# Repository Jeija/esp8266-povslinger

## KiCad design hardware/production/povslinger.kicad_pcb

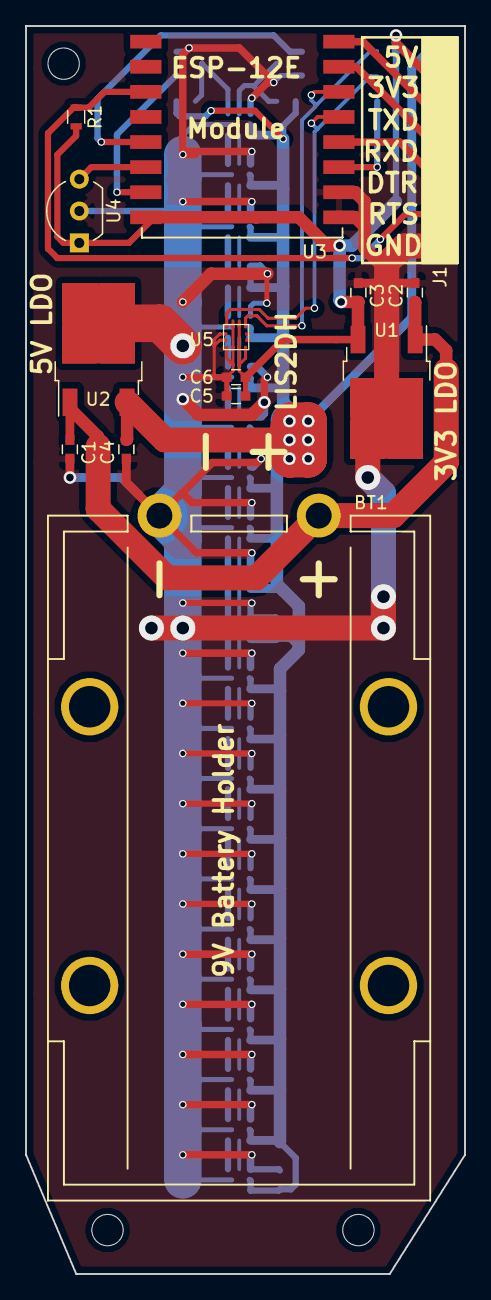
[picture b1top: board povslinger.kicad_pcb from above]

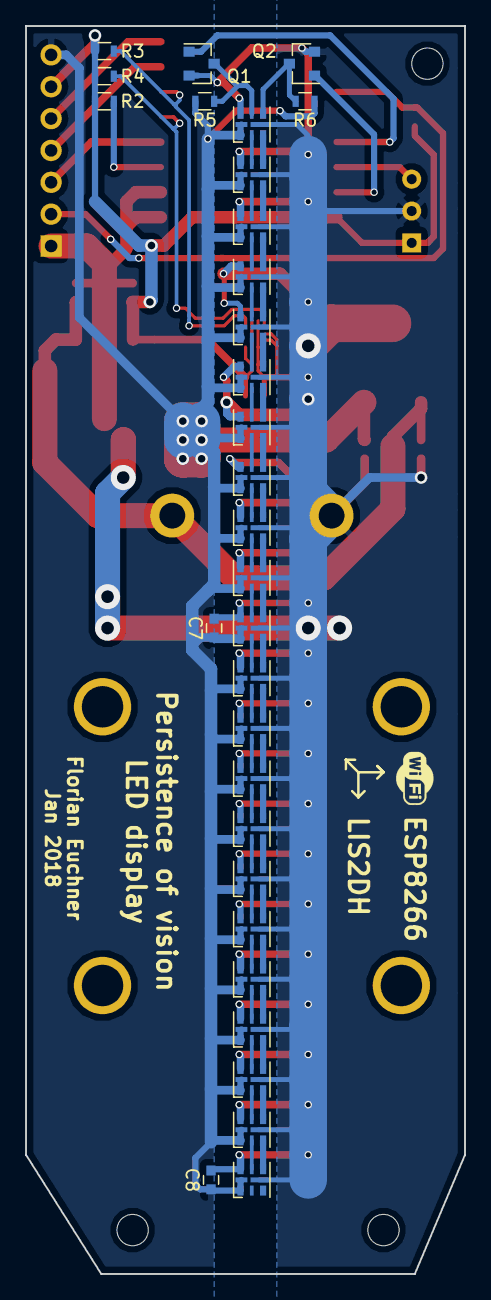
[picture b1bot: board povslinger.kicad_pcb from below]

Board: 2 copper layers, 35.0 x 99.5 mm, 45 parts (31 on the bottom side), 58 nets.

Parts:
BT1: 9V Battery; BatteryHolder_9Volt_Keystone_1294
C1, C2: 330n; C_0603
C3, C4: 4.7u; C_0603
C5: 10n; C_0603
C6, C7, C8: 100n; C_0603
D1, D2, D3, D4, D5, D6, D7, D8, D9, D10, D11, D12, D13, D14, D15, D16, D17, D18, D19, D20, D21, D22: APA102-2020
J1: DEBUG; Pin_Header_Straight_1x07_Pitch2.54mm
Q1, Q2: BSS138; SOT-23
R1, R2, R5, R6: 10K; R_0603
R3, R4: 4K7; R_0603
U1: LF33_TO252; TO-252-2
U2: L7805; TO-252-2
U3: ESP-12E; ESP-12E_SMD
U4: US5881 or similar; TO-92_Inline_Wide
U5: LIS2HH12; LIS2DH12

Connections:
+3V3: C3.1, C5.1, C6.1, J1.6, R1.1, R2.1, R3.1, R4.1, U1.3, U3.8, U4.1, U5.2, U5.9, U5.10
+5V: C4.1, C7.1, C8.1, D1.1, D2.1, D3.1, D4.1, D5.1, D6.1, D7.1, D8.1, D9.1, D10.1, D11.1, D12.1, D13.1, D14.1, D15.1, D16.1, D17.1, D18.1, D19.1, D20.1, D21.1, D22.1, J1.7, R5.1, R6.1, U2.3
+BATT: BT1.1, C1.1, C2.1, U1.1, U2.1
/DTR: J1.3, U3.12
/HALL: U3.6, U4.3
/LEDCLK: Q1.1, U3.5
/LEDCLK_5V: D1.5, Q1.3, R5.2
/LEDDAT: Q2.1, U3.7
/LEDDAT_5V: D1.4, Q2.3, R6.2
/RTS: J1.2, R1.2, U3.3
/RXD: J1.4, U3.15
/SCL: R3.2, U3.14, U5.1
/SDA: R4.2, U3.13, U5.4
/TXD: J1.5, U3.16
GND: BT1.2, C1.2, C2.2, C3.2, C4.2, C5.2, C6.2, C7.2, C8.2, D1.6, D2.6, D3.6, D4.6, D5.6, D6.6, D7.6, D8.6, D9.6, D10.6, D11.6, D12.6, D13.6, D14.6, D15.6, D16.6, D17.6, D18.6, D19.6, D20.6, D21.6, D22.6, J1.1, Q1.2, Q2.2, U1.2, U2.2, U3.9, U3.10, U4.2, U5.3, U5.5, U5.6, U5.7, U5.8
unnamed: D1.2, D2.5
unnamed: D1.3, D2.4
unnamed: D2.2, D3.5
unnamed: D2.3, D3.4
unnamed: D3.2, D4.5
unnamed: D3.3, D4.4
unnamed: D4.2, D5.5
unnamed: D4.3, D5.4
unnamed: D5.2, D6.5
unnamed: D5.3, D6.4
unnamed: D6.2, D7.5
unnamed: D6.3, D7.4
unnamed: D7.2, D8.5
unnamed: D7.3, D8.4
unnamed: D8.2, D9.5
unnamed: D8.3, D9.4
unnamed: D10.2, D11.5
unnamed: D10.3, D11.4
unnamed: D9.3, D10.4
unnamed: D9.2, D10.5
unnamed: D11.2, D12.5
unnamed: D11.3, D12.4
unnamed: D12.2, D13.5
unnamed: D12.3, D13.4
unnamed: D13.2, D14.5
unnamed: D13.3, D14.4
unnamed: D14.2, D15.5
unnamed: D14.3, D15.4
unnamed: D15.2, D16.5
unnamed: D15.3, D16.4
unnamed: D16.2, D17.5
unnamed: D16.3, D17.4
unnamed: D17.2, D18.5
unnamed: D17.3, D18.4
unnamed: D18.2, D19.5
unnamed: D18.3, D19.4
unnamed: D19.2, D20.5
unnamed: D19.3, D20.4
unnamed: D20.2, D21.5
unnamed: D20.3, D21.4
unnamed: D21.2, D22.5
unnamed: D21.3, D22.4
unnamed: R2.2, U3.11

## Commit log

2017-12-31 Initial version control checkin, including:
    * Prototype and production hardware schematic and PCB designs
    * Firmware prototype
    * Debugging output server written in python
    * 3D model for PCB and solder paste stencil holder, can e.g. be 3D printed
    * Resources for mathematical models used in firmware (low pass filter + acceleration model)
2018-01-14 Update some resistor values, remove backup schematics
2018-01-15 Firmware: Add menu functionality
2018-01-17 Firmware: Add temperature function
2018-01-17 Firmware: Add hearts pattern function
2018-01-17 Firmware: Add pixel art function
    Production Schematic: Minor layout improvements
2018-01-18 Schematic: Add description, repo link
2018-01-18 Firmware: Add more pixel art
2018-01-20 Firmware: Use DIO by default for flash communication
2018-01-22 Makefile: Fix build / obj directory creation
